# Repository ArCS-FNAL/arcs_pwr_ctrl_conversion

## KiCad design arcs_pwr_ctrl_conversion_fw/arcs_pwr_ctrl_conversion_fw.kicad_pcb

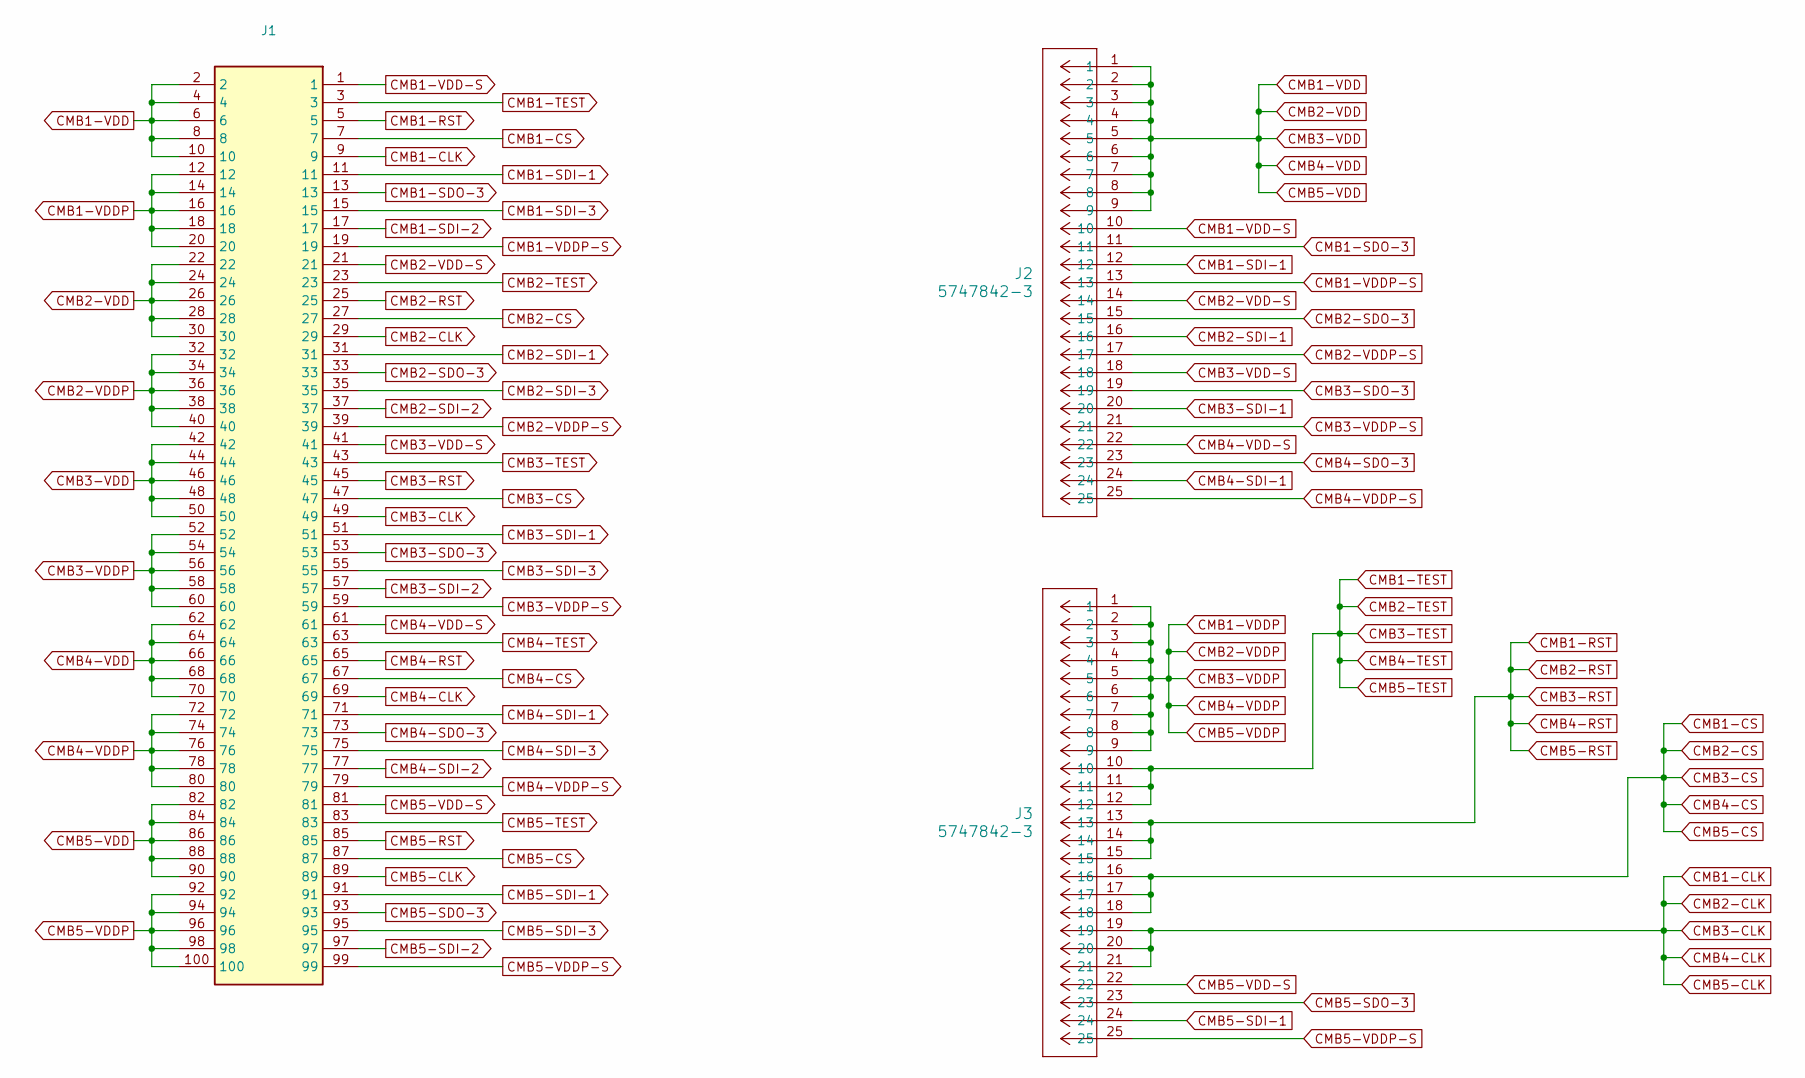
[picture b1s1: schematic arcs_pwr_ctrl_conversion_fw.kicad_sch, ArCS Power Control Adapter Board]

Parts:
J1: 81100-560203-RB; 81100560203RB; Manufacturer_Part_Number 81100-560203-RB; Mouser Part Number 517-81100-560203-RB
J2, J3: 5747842-3; CONN25x1_5747842-3_TEC

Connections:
CMB1-CLK: J1.9, J1.29, J1.49, J1.69, J1.89, J3.19, J3.20, J3.21
CMB1-CS: J1.7, J1.27, J1.47, J1.67, J1.87, J3.16, J3.17, J3.18
CMB1-RST: J1.5, J1.25, J1.45, J1.65, J1.85, J3.13, J3.14, J3.15
CMB1-SDI-1: J1.11, J2.12
CMB1-SDI-2: J1.17
CMB1-SDI-3: J1.15
CMB1-SDO-3: J1.13, J2.11
CMB1-TEST: J1.3, J1.23, J1.43, J1.63, J1.83, J3.10, J3.11, J3.12
CMB1-VDD: J1.2, J1.4, J1.6, J1.8, J1.10, J1.22, J1.24, J1.26, J1.28, J1.30, J1.42, J1.44, J1.46, J1.48, J1.50, J1.62, J1.64, J1.66, J1.68, J1.70, J1.82, J1.84, J1.86, J1.88, J1.90, J2.1, J2.2, J2.3, J2.4, J2.5, J2.6, J2.7, J2.8, J2.9
CMB1-VDD-S: J1.1, J2.10
CMB1-VDDP: J1.12, J1.14, J1.16, J1.18, J1.20, J1.32, J1.34, J1.36, J1.38, J1.40, J1.52, J1.54, J1.56, J1.58, J1.60, J1.72, J1.74, J1.76, J1.78, J1.80, J1.92, J1.94, J1.96, J1.98, J1.100, J3.1, J3.2, J3.3, J3.4, J3.5, J3.6, J3.7, J3.8, J3.9
CMB1-VDDP-S: J1.19, J2.13
CMB2-SDI-1: J1.31, J2.16
CMB2-SDI-2: J1.37
CMB2-SDI-3: J1.35
CMB2-SDO-3: J1.33, J2.15
CMB2-VDD-S: J1.21, J2.14
CMB2-VDDP-S: J1.39, J2.17
CMB3-SDI-1: J1.51, J2.20
CMB3-SDI-2: J1.57
CMB3-SDI-3: J1.55
CMB3-SDO-3: J1.53, J2.19
CMB3-VDD-S: J1.41, J2.18
CMB3-VDDP-S: J1.59, J2.21
CMB4-SDI-1: J1.71, J2.24
CMB4-SDI-2: J1.77
CMB4-SDI-3: J1.75
CMB4-SDO-3: J1.73, J2.23
CMB4-VDD-S: J1.61, J2.22
CMB4-VDDP-S: J1.79, J2.25
CMB5-SDI-1: J1.91, J3.24
CMB5-SDI-2: J1.97
CMB5-SDI-3: J1.95
CMB5-SDO-3: J1.93, J3.23
CMB5-VDD-S: J1.81, J3.22
CMB5-VDDP-S: J1.99, J3.25

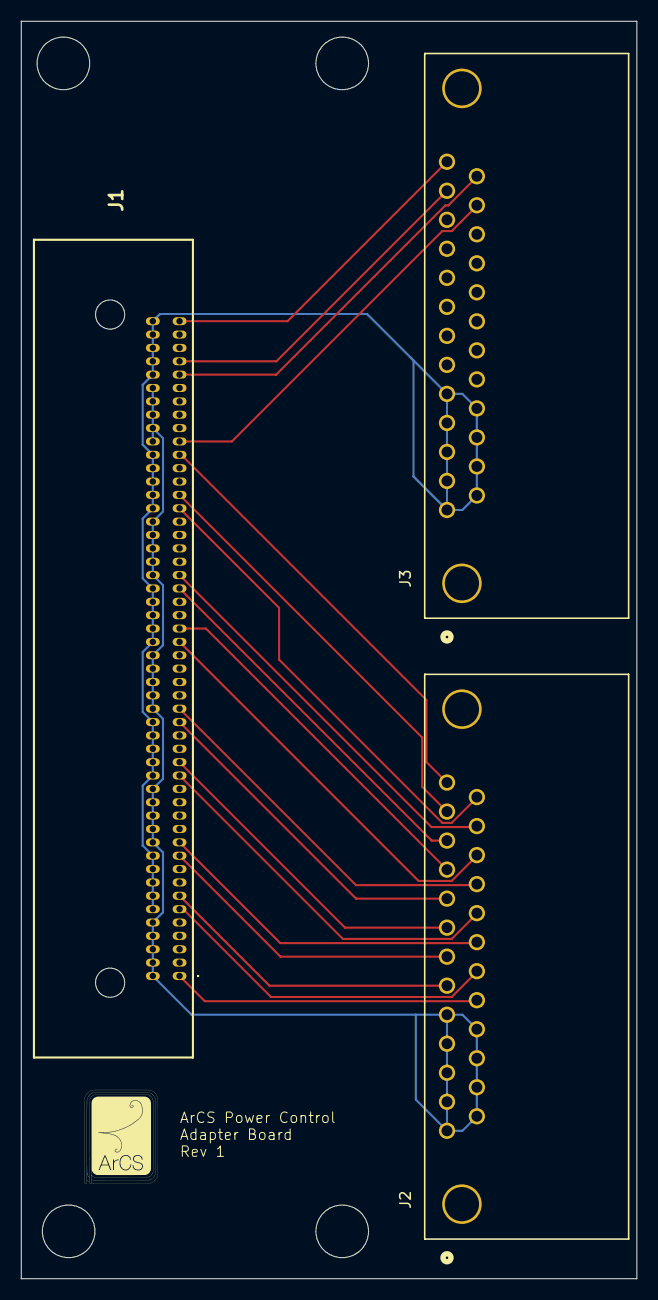
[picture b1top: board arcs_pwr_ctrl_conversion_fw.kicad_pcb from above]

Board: 4 copper layers, 58.5 x 119.5 mm, 3 parts (0 on the bottom side), 26 nets.

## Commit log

2024-07-12 clean up
2024-07-16 Add Rev 1
2024-07-17 Rev 1
